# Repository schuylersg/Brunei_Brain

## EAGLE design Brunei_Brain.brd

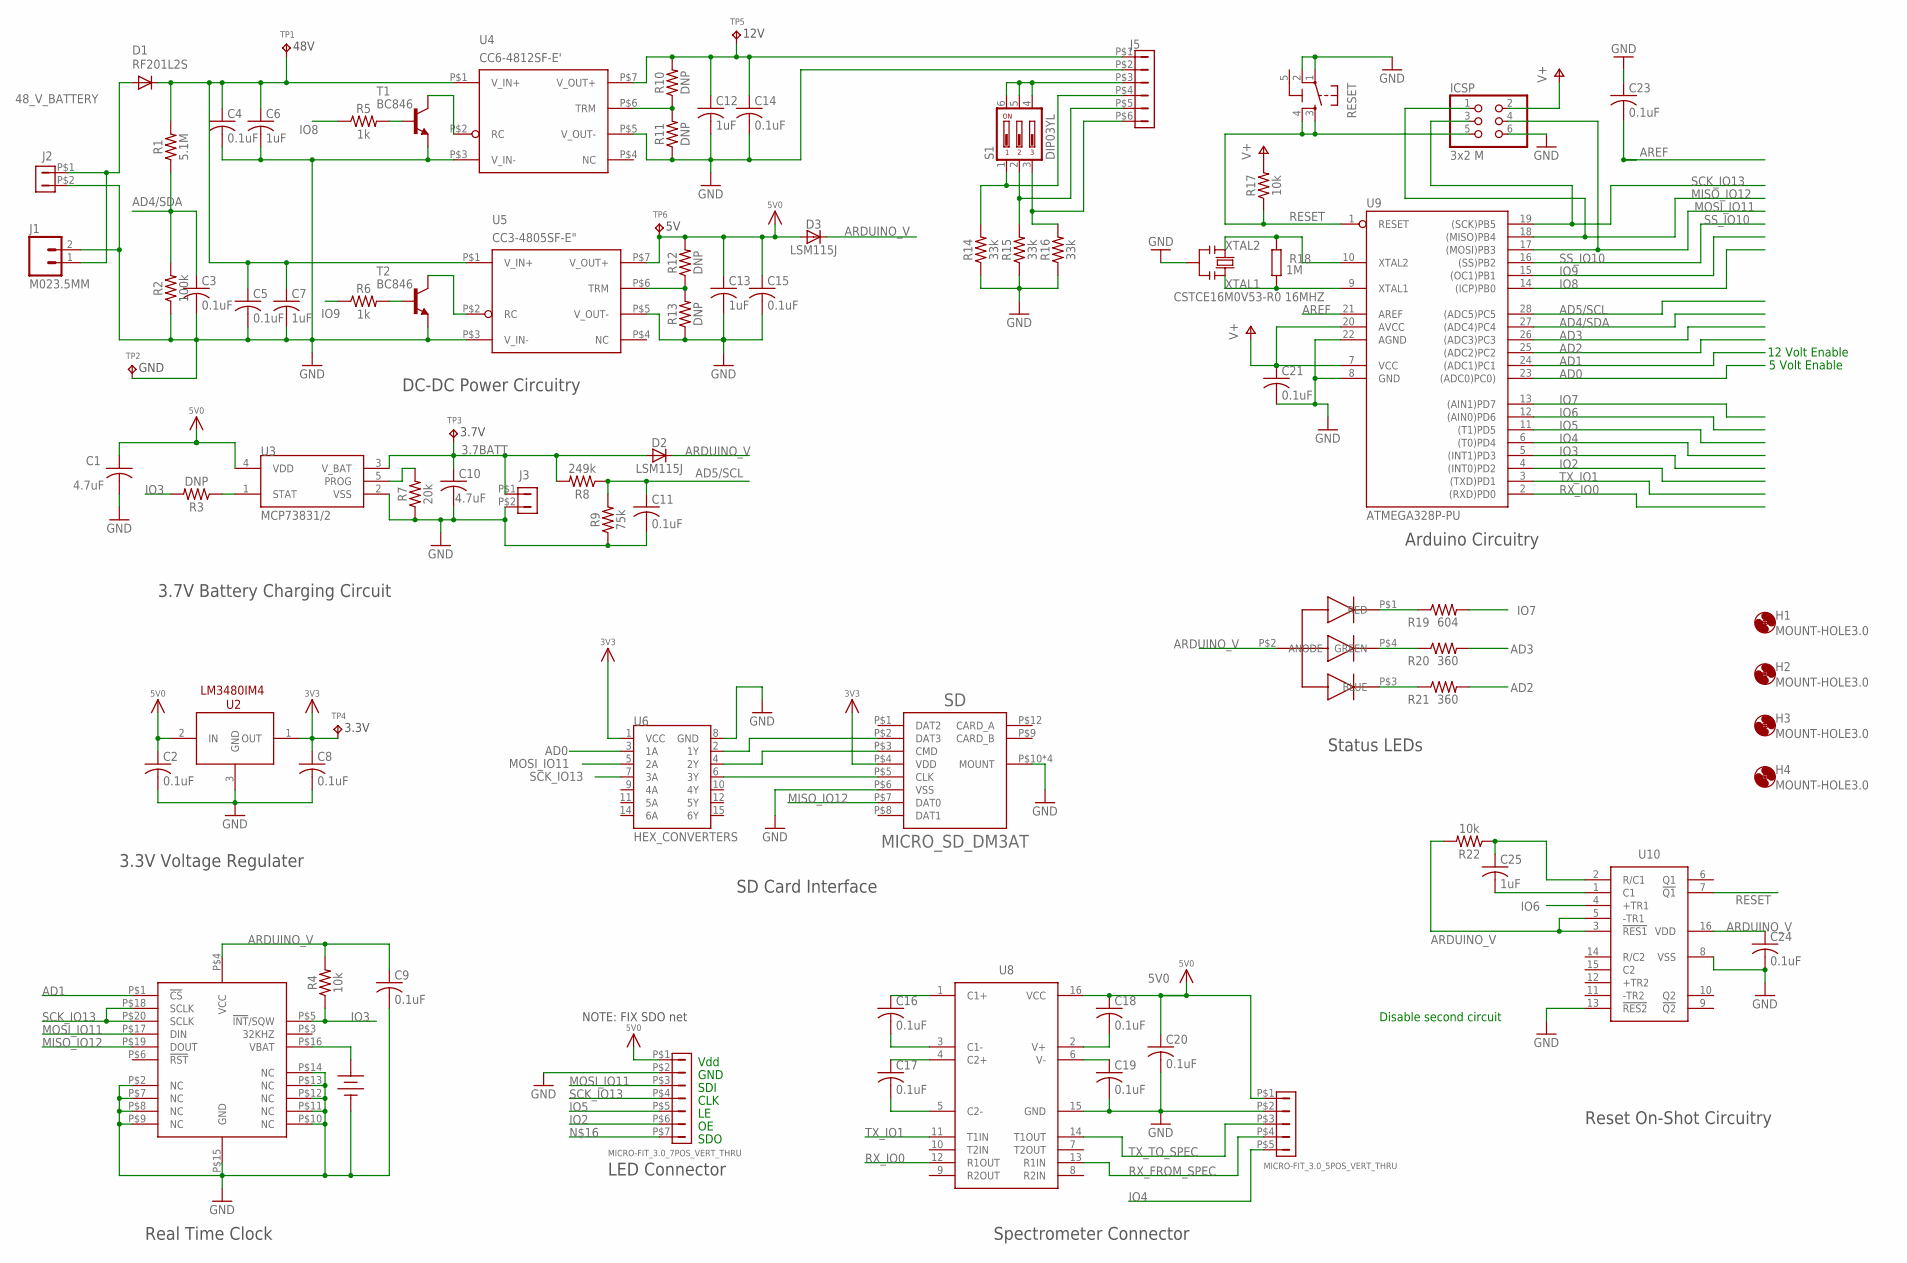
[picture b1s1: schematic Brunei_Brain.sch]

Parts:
B1: BATTERY_12MM; KEYSTONE_12MM_BATT_SM
C1, C10: 4.7uF; C0603; PARTNUMBER 445-5178-1-ND
C2, C3, C4, C5, C8, C9, C11, C14, C15, C16, C17, C18, C19, C20, C21, C23, C24: 0.1uF; C0603; PARTNUMBER 311-1523-1-ND
C6, C7, C12, C13, C25: 1uF; C1206; PARTNUMBER 1276-2747-1-ND
D1: RF201L2S; SOD-106
D2, D3: LSM115J; DO-214BA
D4: RGB_LED_COMMON_ANODE_1; PLCC-4
H1, H2, H3, H4: MOUNT-HOLE3.0; 3,0
ICSP: 3x2 M; 2X03
J1: M023.5MM; SCREWTERMINAL-3.5MM-2; MANPARTNUMBER 1984617
J2, J3: MICRO-FIT_3.0_2POS_VERT_THRU; MICRO-FIT_3.0_2POS_VERT_THROUGH
J4: MICRO-FIT_3.0_7POS_VERT_THRU; MICRO-FIT_3.0_7POS_VERT_THROUGH
J5: MICRO-FIT_3.0_6POS_VERT_THRU; MICRO-FIT_3.0_6POS_VERT_THROUGH
J6: MICRO-FIT_3.0_5POS_VERT_THRU; MICRO-FIT_3.0_5POS_VERT_THROUGH
R1: 5.1M; 0603-RES; PARTNUMBER 541-5.10MHCT-ND
R2: 100k; 0603-RES; PARTNUMBER 1276-3486-1-ND
R3, R10, R11, R12, R13: DNP; 0603-RES
R4, R17, R22: 10k; 0603-RES; PARTNUMBER 311-10.0KHRCT-ND
R5, R6: 1k; 0603-RES; PARTNUMBER 1276-5062-1-ND
R7: 20k; 0603-RES; PARTNUMBER 1276-4768-1-ND
R8: 249k; 0603-RES; PARTNUMBER 311-249KHRCT-ND
R9: 75k; 0603-RES; PARTNUMBER 311-75.0KHRCT-ND
R14, R15, R16: 33k; 0603-RES; PARTNUMBER 311-33KGRCT-ND
R18: 1M; R0603-ROUND; PARTNUMBER P1.00MHCT-ND
R19: 604; 0603-RES; PARTNUMBER 1276-3506-1-ND
R20, R21: 360; 0603-RES; PARTNUMBER 1276-5051-1-ND
RESET: TS42031-160R-TR-7260; TS42; PARTNUMBER 450-1759-1-ND
S1: DIP03YL
SD: MICRO_SD_DM3AT; MICROSD_DM3AT
T1, T2: BC846; SOT23; PARTNUMBER MMBT2484LT1GOSCT-ND
TP1, TP2, TP3, TP4, TP5, TP6: TPPAD1-13; P1-13
U1: DS3234; SOIC-20_MAXIM
U2: LM3480IM4; SOT23-3
U3: MCP73831/2; SOT23-5
U4: CC6-4812SF-E'; CC6-XXXXXF-E
U5: CC3-4805SF-E"; CC3-XXXXXF-E
U6: HEX_CONVERTERS; SO-16_SSG; PARTNUMBER 568-1453-5-ND
U8: ST232; SO-16_SSG
U9: ATMEGA328P-PU; DIL28-3; PARTNUMBER ATMEGA328P-PN-ND
U10: MULTIVIBRATOR_DUAL; SO-16_SSG
Y1: CSTCE16M0V53-R0 16MHZ; RESONATOR; PARTNUMBER 490-1198-1-ND

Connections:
3.7BATT: C10.1, D2.P$1 (A), J3.P$1, R8.2, TP3.TP, U3.3 (V_BAT)
3V3: C8.1, SD.P$4 (VDD), TP4.TP, U2.1 (OUT), U6.1 (VCC)
5-GND: RESET.5 (5-GND)
5V0: C1.1, C2.1, C13.1, C15.1, C18.1, C20.1, D3.P$1 (A), J4.P$1, J6.P$1, R12.2, TP6.TP, U2.2 (IN), U3.4 (VDD), U5.P$7 (V_OUT+), U8.16 (VCC)
12V: C12.1, C14.1, J5.P$1, R10.2, TP5.TP, U4.P$7 (V_OUT+)
48V: C4.1, C5.1, C6.1, C7.1, D1.P$2 (C), R1.2, TP1.TP, U4.P$1 (V_IN+), U5.P$1 (V_IN+)
48_V_BATTERY: D1.P$1 (A), J1.1, J2.P$1
AD0: U6.3 (1A), U9.23 ((ADC0)PC0))
AD1: U1.P$1 (!CS), U9.24 ((ADC1)PC1)
AD2: R21.2, U9.25 ((ADC2)PC2)
AD3: R20.2, U9.26 ((ADC3)PC3)
AD4/SDA: C3.1, R1.1, R2.2, U9.27 ((ADC4)PC4)
AD5/SCL: C11.1, R8.1, R9.2, U9.28 ((ADC5)PC5)
ARDUINO_V: C9.1, C21.1, C24.1, D2.P$2 (C), D3.P$2 (C), D4.P$2 (ANODE), ICSP.2, R4.2, R17.2, R22.2, U1.P$4 (VCC), U9.7 (VCC), U9.20 (AVCC), U10.3 (!RES1), U10.5 (-TR1), U10.16 (VDD)
AREF: C23.2, U9.21 (AREF)
DEUTERIUM_ENABLE: J5.P$4, R14.2, S1.1
GND: B1.P$3 (V-), C1.2, C2.2, C3.2, C4.2, C5.2, C6.2, C7.2, C8.2, C9.2, C10.2, C11.2, C12.2, C13.2, C14.2, C15.2, C19.2, C20.2, C21.2, C23.1, C24.2, ICSP.6, J1.2, J2.P$2, J3.P$2, J4.P$2, J5.P$2, J6.P$2, R2.1, R7.1, R9.1, R11.1, R13.1, R14.1, R15.1, R16.1, RESET.1, RESET.2, SD.P$6 (VSS), SD.P$10 (MOUNT), SD.P$11 (MOUNT), SD.P$13 (MOUNT), SD.P$14 (MOUNT), T1.2 (E), T2.2 (E), TP2.TP, U1.P$2 (NC), U1.P$7 (NC), U1.P$8 (NC), U1.P$9 (NC), U1.P$10 (NC), U1.P$11 (NC), U1.P$12 (NC), U1.P$13 (NC), U1.P$14 (NC), U1.P$15 (GND), U2.3 (GND), U3.2 (VSS), U4.P$3 (V_IN-), U4.P$5 (V_OUT-), U5.P$3 (V_IN-), U5.P$5 (V_OUT-), U6.8 (GND), U8.15 (GND), U9.8 (GND), U9.22 (AGND), U10.8 (VSS), U10.13 (!RES2), Y1.2
IO2: J4.P$6, U9.4 ((INT0)PD2)
IO3: R3.2, R4.1, U1.P$5 (!INT!/SQW), U9.5 ((INT1)PD3)
IO4: J6.P$5, U9.6 ((T0)PD4)
IO5: J4.P$5, U9.11 ((T1)PD5)
IO6: U9.12 ((AIN0)PD6), U10.4 (+TR1)
IO7: R19.2, U9.13 ((AIN1)PD7)
IO8: R5.1, U9.14 ((ICP)PB0)
IO9: R6.1, U9.15 ((OC1)PB1)
LAMP_5V: J5.P$3, S1.4, S1.5, S1.6
MISO_IO12: ICSP.1, SD.P$7 (DAT0), U1.P$19 (DOUT), U9.18 ((MISO)PB4)
MOSI_IO11: ICSP.4, J4.P$3, U1.P$17 (DIN), U6.5 (2A), U9.17 ((MOSI)PB3)
unnamed: T2.3 (C), U5.P$2 (RC)
unnamed: T1.3 (C), U4.P$2 (RC)
unnamed: R5.2, T1.1 (B)
unnamed: R6.2, T2.1 (B)
unnamed: R12.1, R13.2, U5.P$6 (TRM)
unnamed: B1.P$1 (V+), B1.P$2 (V+), U1.P$16 (VBAT)
unnamed: R7.2, U3.5 (PROG)
unnamed: SD.P$3 (CMD), U6.4 (2Y)
unnamed: SD.P$5 (CLK), U6.6 (3Y)
unnamed: R3.1, U3.1 (STAT)
unnamed: C25.2, U10.1 (C1)
unnamed: C25.1, R22.1, U10.2 (R/C1)
unnamed: D4.P$1 (RED), R19.1
unnamed: D4.P$4 (GREEN), R20.1
unnamed: D4.P$3 (BLUE), R21.1
unnamed: C16.1, U8.1 (C1+)
unnamed: R10.1, R11.2, U4.P$6 (TRM)
unnamed: C16.2, U8.3 (C1-)
unnamed: C17.1, U8.4 (C2+)
unnamed: C17.2, U8.5 (C2-)
unnamed: C19.1, U8.6 (V-)
unnamed: C18.2, U8.2 (V+)
unnamed: SD.P$2 (DAT3), U6.2 (1Y)
RESET: ICSP.5, R17.1, RESET.3, RESET.4, U9.1 (RESET), U10.7 (!Q1)
RX_FROM_SPEC: J6.P$4, U8.13 (R1IN)
RX_IO0: U8.12 (R1OUT), U9.2 ((RXD)PD0)
SCK_IO13: ICSP.3, J4.P$4, U1.P$18 (SCLK), U1.P$20 (SCLK), U6.7 (3A), U9.19 ((SCK)PB5)
SHUTTER_ENABLE: J5.P$6, R16.2, S1.3
SS_IO10: U9.16 ((SS)PB2)
TUNGSTEN_ENABLE: J5.P$5, R15.2, S1.2
TX_IO1: U8.11 (T1IN), U9.3 ((TXD)PD1)
TX_TO_SPEC: J6.P$3, U8.14 (T1OUT)
XTAL1: R18.1, U9.9 (XTAL1), Y1.3
XTAL2: R18.2, U9.10 (XTAL2), Y1.1

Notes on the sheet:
DC-DC Power Circuitry
Arduino Circuitry
3.7V Battery Charging Circuit
3.3V Voltage Regulater
SD Card Interface
Real Time Clock
LED Connector
Spectrometer Connector
Reset On-Shot Circuitry
Status LEDs
Vdd
GND
SDI
CLK
SDO
Disable second circuit
5 Volt Enable
12 Volt Enable
NOTE: FIX SDO net

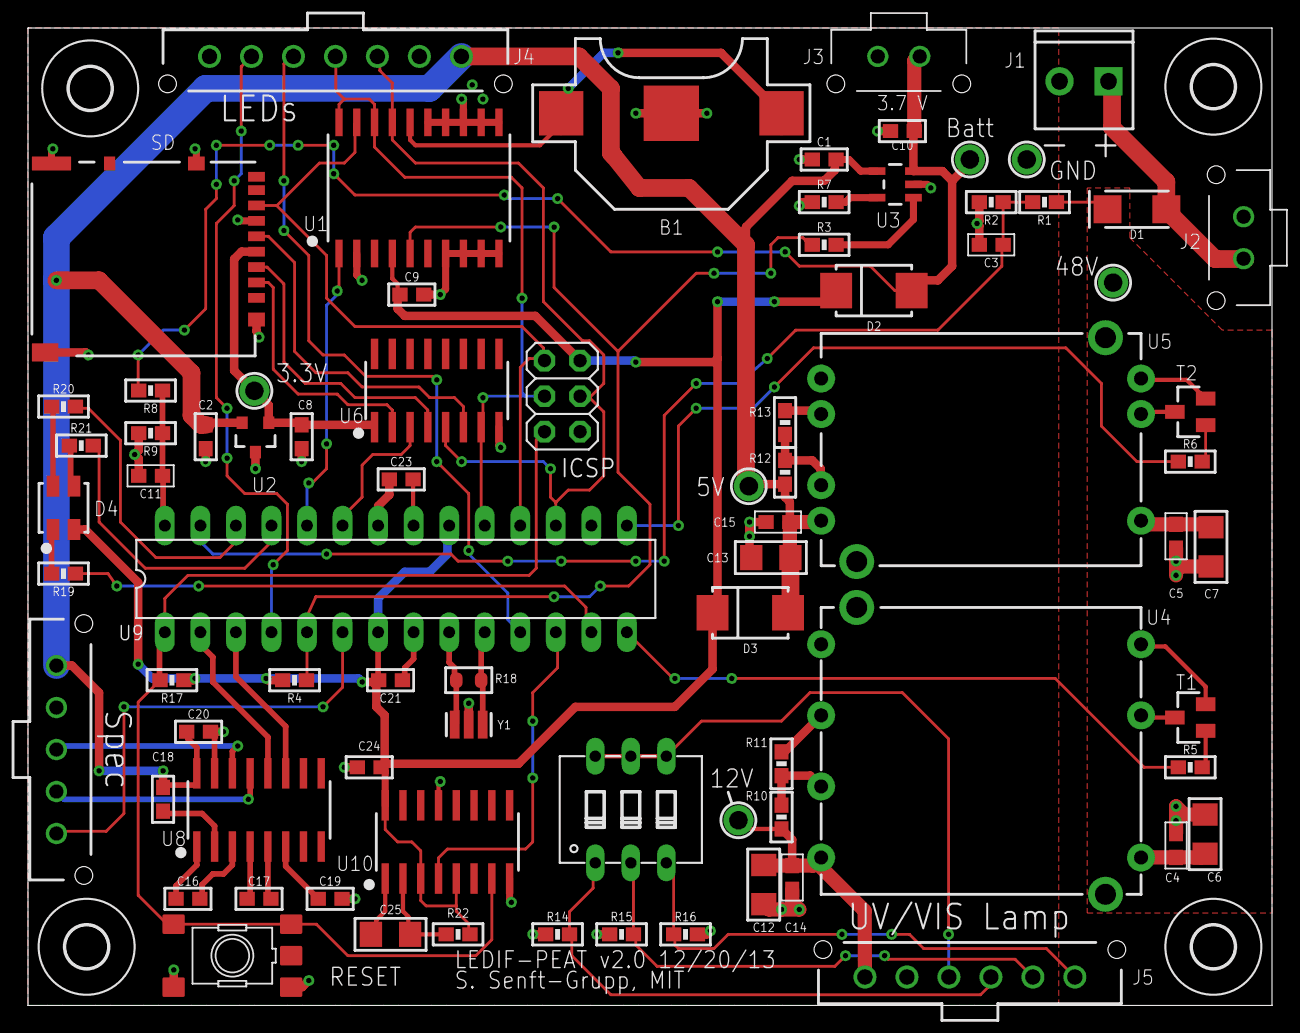
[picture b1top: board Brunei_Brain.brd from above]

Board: 2 copper layers, 88.9 x 69.8 mm, 83 parts (0 on the bottom side), 60 nets.

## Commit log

2013-11-21 Version 1
2013-11-21 Start of branch v2
2013-11-27 Started v2 update process.
2013-12-17 some continuing updates
2013-12-21 Version 2.0 Complete
2014-01-03 Updated part attributes for ordering
2014-01-03 Quick update.

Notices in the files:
parts and their libraries:
SparkFun-Passives: Licensing: CC v3.0 Share-Alike You are welcome to use this library for commercial purposes.
